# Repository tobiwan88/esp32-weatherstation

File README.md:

# esp32-weatherstation

Solar + USB powered ESP32-S3 air-quality weather station: temperature, humidity, CO2, particulate matter (PM1/2.5/4/10) and a NOx index,
reported over WiFi. Custom 4-layer PCB assembled by JLCPCB. Work in progress: hardware requirements, BOM and checks are in place; layout and firmware come next.

| Part | What |
|---|---|
| MCU | ESP32-S3-WROOM-1-N8, deep-sleep duty cycle (10-15 min) |
| Sensors | Sensirion SEN66 (PM, CO2, T/RH, VOC/NOx index), outdoor SHT45 in a radiation shield, spare Qwiic port |
| Power | one protected 18650, solar MPPT (CN3791) **or** USB-C (TP4056) charging, AP2112K 3.3 V LDO |
| Debug | USB-C native USB-JTAG/serial, UART0 header, test points |
| NO2 | not on v1 (optional external module later) |

Estimated cost: about EUR 240-300 for the first batch (5 boards) plus one complete station, about EUR 133 for each further station
(see `hardware/weatherstation-v1/REQUIREMENTS.md`, section 5a).

## Where to look
- `hardware/weatherstation-v1/`: `REQUIREMENTS.md`, `BOARD.md`, `bom.csv`, `ORDER.md`, `board.yaml`, `parts/`
- `hardware/PLAN.md`: done and next steps. `hardware/README.md`: map of the hardware tree.
- `.claude/skills/`: hardware agent skills (`hw-base`, `kicad-schematic`, `kicad-layout`, `hw-parts`); `CLAUDE.md`: agent notes.
- `scripts/check.sh`: gate (hardware checks, tests, privacy scan).

Base derived from [desk_notifier](https://github.com/tobiwan88/desk_notifier) (hardware skills, calc scripts, tools). MIT license.

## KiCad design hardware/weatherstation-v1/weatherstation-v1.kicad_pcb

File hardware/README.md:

# Hardware: where to look

Board profile: **`weatherstation-v1/`** (requirements, BOM, datasheet cards, order checklist). Pre-layout: no KiCad project yet.

| What | Where |
|---|---|
| Requirements (function, electrical, thermal, EMC, USB, manufacturing, cost) | `weatherstation-v1/REQUIREMENTS.md` |
| BOM with LCSC numbers and verification status | `weatherstation-v1/bom.csv` |
| Board notes, decisions, open items, commands | `weatherstation-v1/BOARD.md` |
| Facts the scripts read | `weatherstation-v1/board.yaml`, `critical.yaml`, `parts/` |
| Order checklist, bring-up | `weatherstation-v1/ORDER.md` |
| Plan and next steps | `PLAN.md` |
| Board-neutral checks | `calc/` (`bom_check.py`, `power_budget.py`, `critical.py`, `buck.py`, `impedance.py`, `pcb.py`) |
| Stock lookup, DRC summary | `tools/` (`jlcparts.py`, `drc_summary.py`) |
| Fab design floors | `rules/` |
| Helper-agent prompts | `agents/` |
| Working KiCad pipeline to copy from (desk_notifier) | `reference/desk_notifier/` |

Agent skills (board-neutral): `hw-base` (read first), `kicad-schematic`, `kicad-layout`, `hw-parts` in `.claude/skills/`.

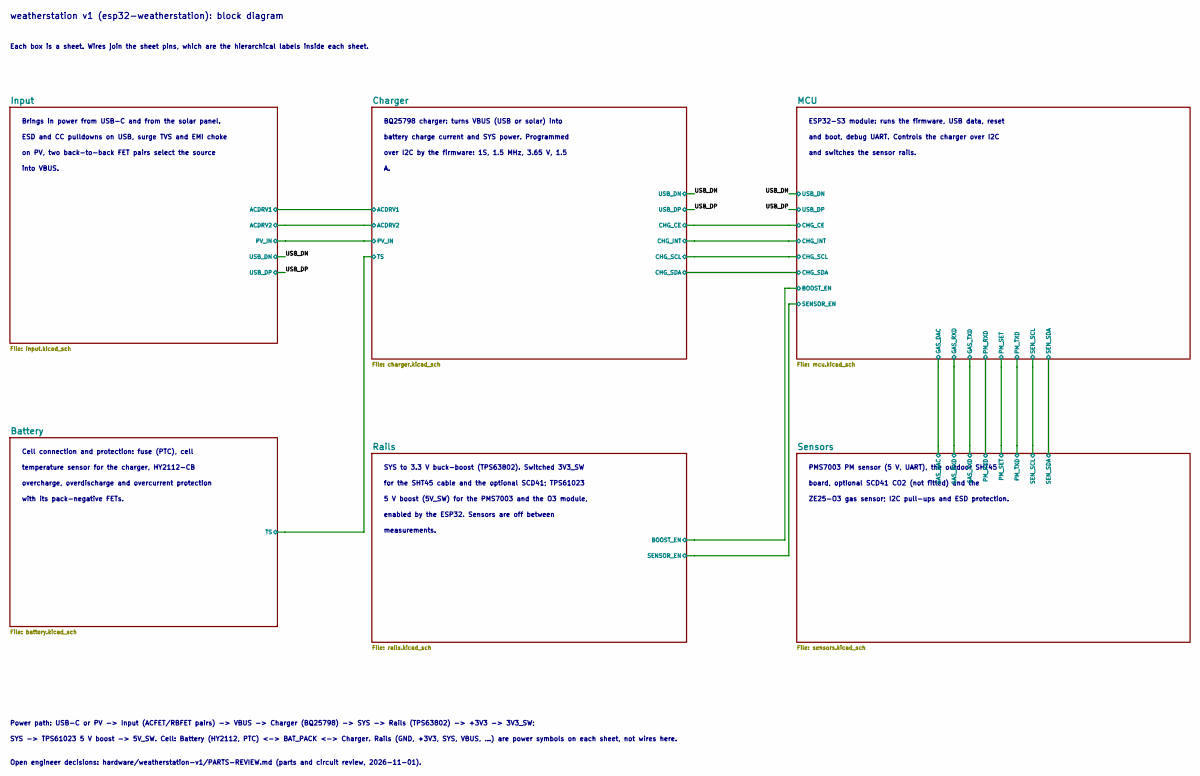
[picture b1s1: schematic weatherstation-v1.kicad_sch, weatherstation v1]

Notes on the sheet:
weatherstation v1 (esp32-weatherstation): block diagram
Each box is a sheet. Wires join the sheet pins, which are the hierarchical labels inside each sheet.
Power path: USB-C or PV -> Input (ACFET/RBFET pairs) -> VBUS -> Charger (BQ25798) -> SYS -> Rails (TPS63802) -> +3V3 -> 3V3_SW;
SYS -> TPS61023 5 V boost -> 5V_SW. Cell: Battery (HY2112, PTC) <-> BAT_PACK <-> Charger. Rails (GND, +3V3, SYS, VBUS, ...) are power symbols on each sheet, not wires here.
Open engineer decisions: hardware/weatherstation-v1/PARTS-REVIEW.md (parts and circuit review, 2026-11-01).
Brings in power from USB-C and from the solar panel.
ESD and CC pulldowns on USB, surge TVS and EMI choke
on PV, two back-to-back FET pairs select the source
into VBUS.
BQ25798 charger: turns VBUS (USB or solar) into
battery charge current and SYS power. Programmed
over I2C by the firmware: 1S, 1.5 MHz, 3.65 V, 1.5
Cell connection and protection: fuse (PTC), cell
temperature sensor for the charger, HY2112-CB
overcharge, overdischarge and overcurrent protection
with its pack-negative FETs.
ESP32-S3 module: runs the firmware, USB data, reset
and boot, debug UART. Controls the charger over I2C
and switches the sensor rails.
SYS to 3.3 V buck-boost (TPS63802). Switched 3V3_SW
for the SHT45 cable and the optional SCD41; TPS61023
5 V boost (5V_SW) for the PMS7003 and the O3 module,
enabled by the ESP32. Sensors are off between
measurements.
PMS7003 PM sensor (5 V, UART), the outdoor SHT45
board, optional SCD41 CO2 (not fitted) and the
ZE25-O3 gas sensor; I2C pull-ups and ESD protection.

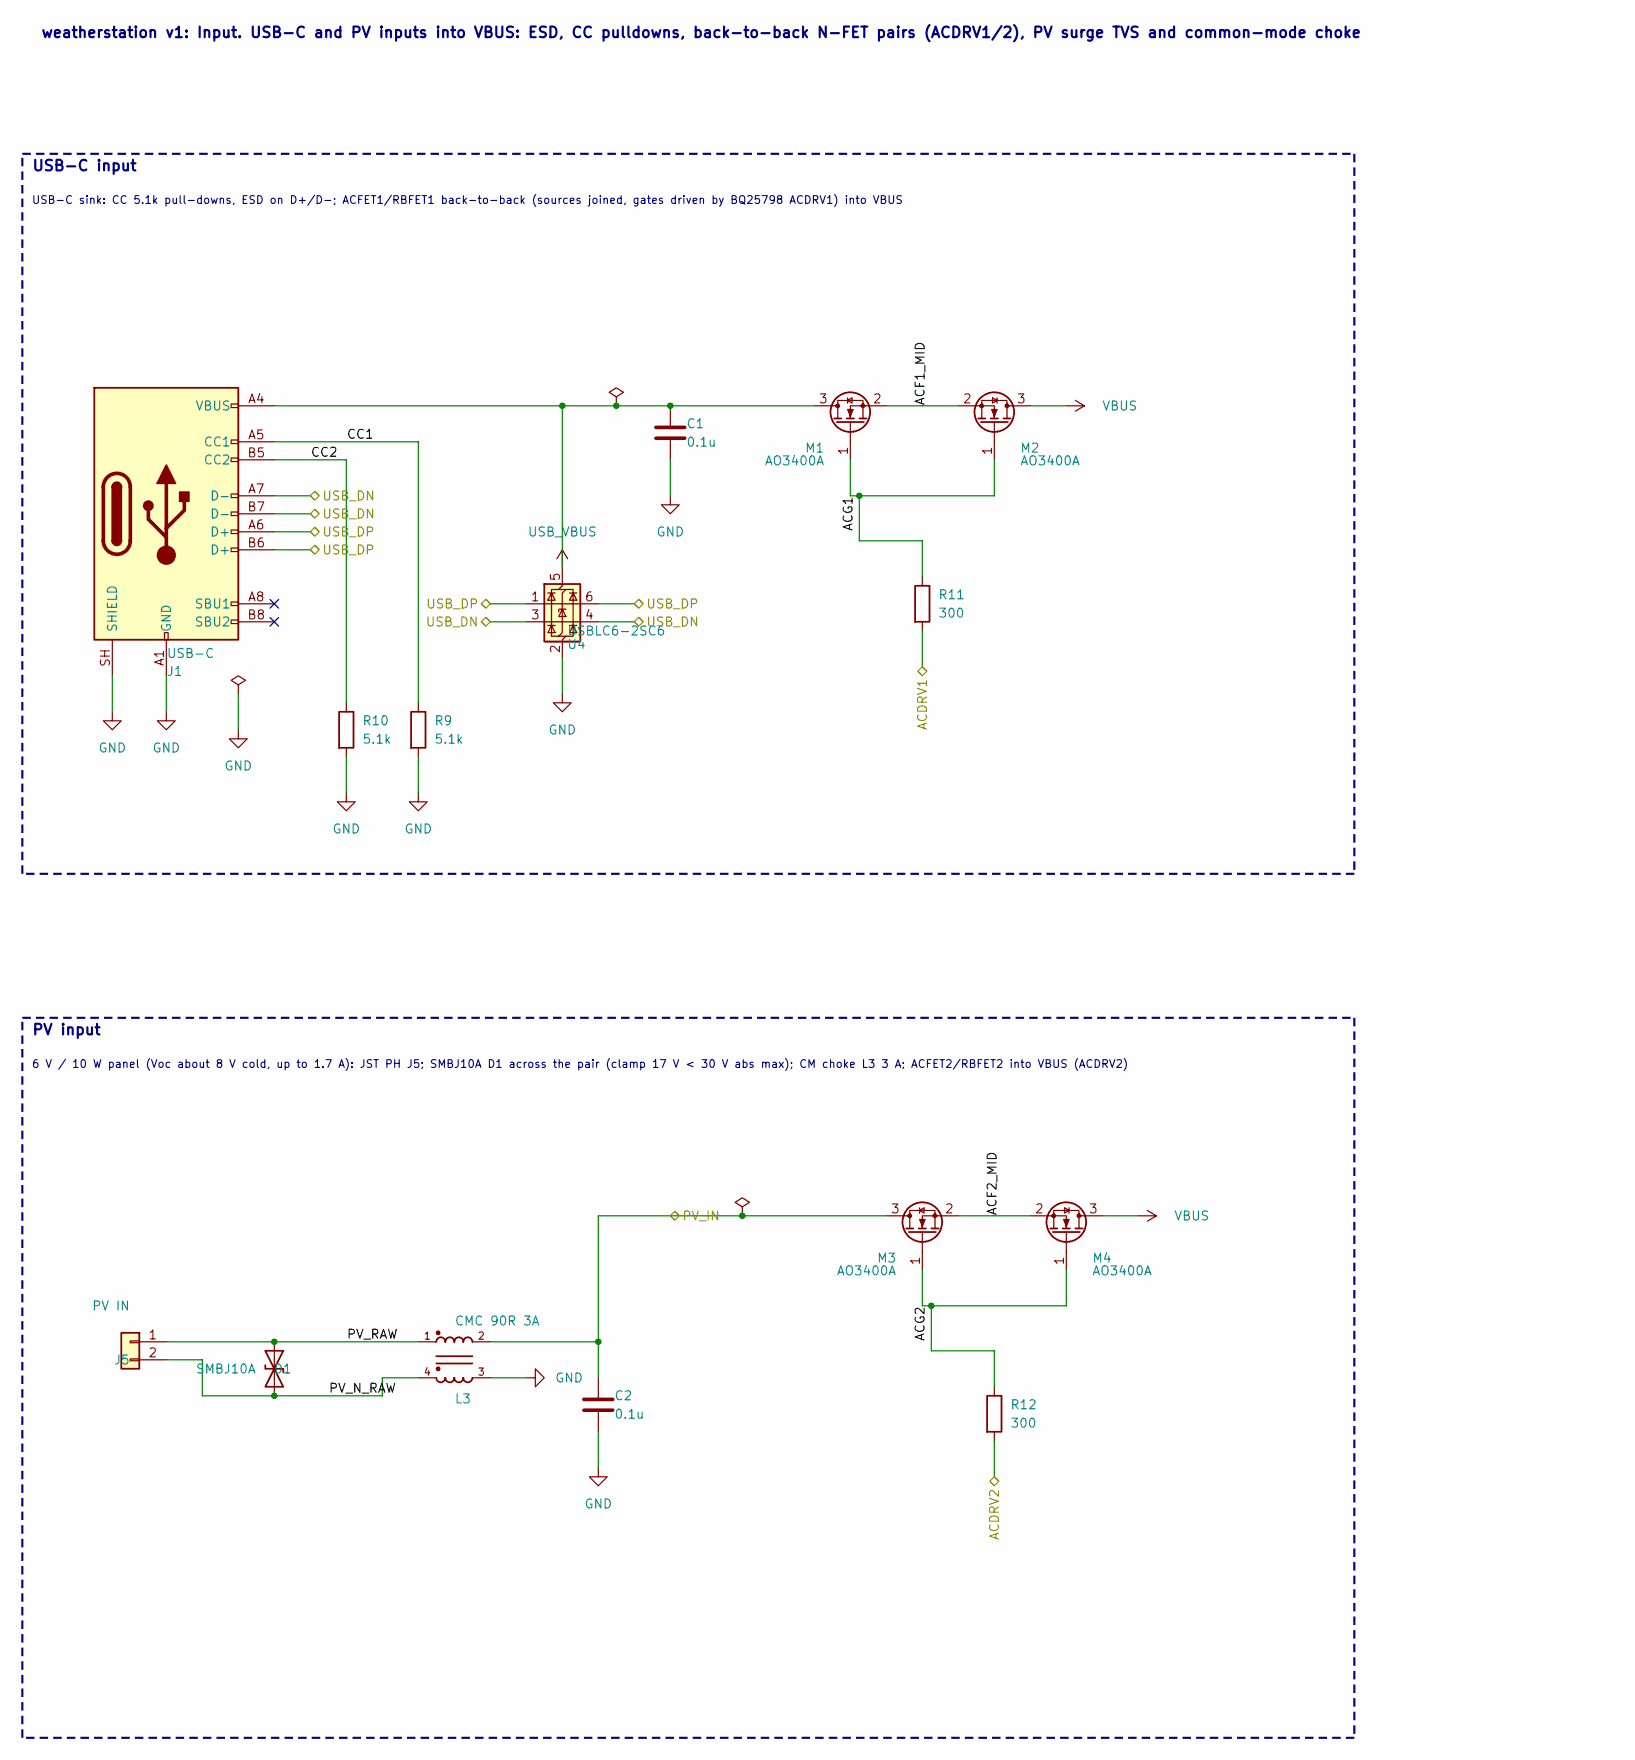
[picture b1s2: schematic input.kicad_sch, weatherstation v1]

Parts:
C1, C2: 0.1u; C_0402_1005Metric; LCSC C307331
D1: SMBJ10A; D_SMB; LCSC C151250
J1: USB-C; USB_C_Receptacle_HRO_TYPE-C-31-M-12; LCSC C165948
J5: PV IN; JST_PH_B2B-PH-K_1x02_P2.00mm_Vertical
L3: CMC 90R 3A; CMF4532F_4P; LCSC C963746
M1, M2, M3, M4: AO3400A; SOT-23; LCSC C20917
R9, R10: 5.1k; R_0402_1005Metric; LCSC C25905
R11, R12: 300; R_0603_1608Metric; LCSC C23025
U4: USBLC6-2SC6; SOT-23-6; LCSC C7519

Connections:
/Charger/ACDRV1: R11.2; also elsewhere on the board
/Charger/ACDRV2: R12.2; also elsewhere on the board
/Charger/PV_IN: C2.1, L3.2, M3.3 (D); also elsewhere on the board
/Input/ACF1_MID: M1.2 (S), M2.2 (S)
/Input/ACF2_MID: M3.2 (S), M4.2 (S)
/Input/ACG1: M1.1 (G), M2.1 (G), R11.1
/Input/ACG2: M3.1 (G), M4.1 (G), R12.1
/Input/CC1: J1.A5 (CC1), R9.1
/Input/CC2: J1.B5 (CC2), R10.1
/Input/PV_N_RAW: D1.2 (A2), J5.2, L3.4
/Input/PV_RAW: D1.1 (A1), J5.1, L3.1
/USB_DN: J1.A7 (D-), J1.B7 (D-), U4.3 (I/O2), U4.4 (I/O2); also elsewhere on the board
/USB_DP: J1.A6 (D+), J1.B6 (D+), U4.1 (I/O1), U4.6 (I/O1); also elsewhere on the board
GND: C1.2, C2.2, J1.A1 (GND), J1.A12 (GND), J1.B1 (GND), J1.B12 (GND), J1.SH (SHIELD), L3.3, R9.2, R10.2, U4.2 (GND); also elsewhere on the board
USB_VBUS: C1.1, J1.A4 (VBUS), J1.A9 (VBUS), J1.B4 (VBUS), J1.B9 (VBUS), M1.3 (D), U4.5 (VBUS); also elsewhere on the board
VBUS: M2.3 (D), M4.3 (D); also elsewhere on the board

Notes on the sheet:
USB-C input
USB-C sink: CC 5.1k pull-downs, ESD on D+/D-; ACFET1/RBFET1 back-to-back (sources joined, gates driven by BQ25798 ACDRV1) into VBUS
PV input
6 V / 10 W panel (Voc about 8 V cold, up to 1.7 A): JST PH J5; SMBJ10A D1 across the pair (clamp 17 V < 30 V abs max); CM choke L3 3 A; ACFET2/RBFET2 into VBUS (ACDRV2)
weatherstation v1: Input. USB-C and PV inputs into VBUS: ESD, CC pulldowns, back-to-back N-FET pairs (ACDRV1/2), PV surge TVS and common-mode choke

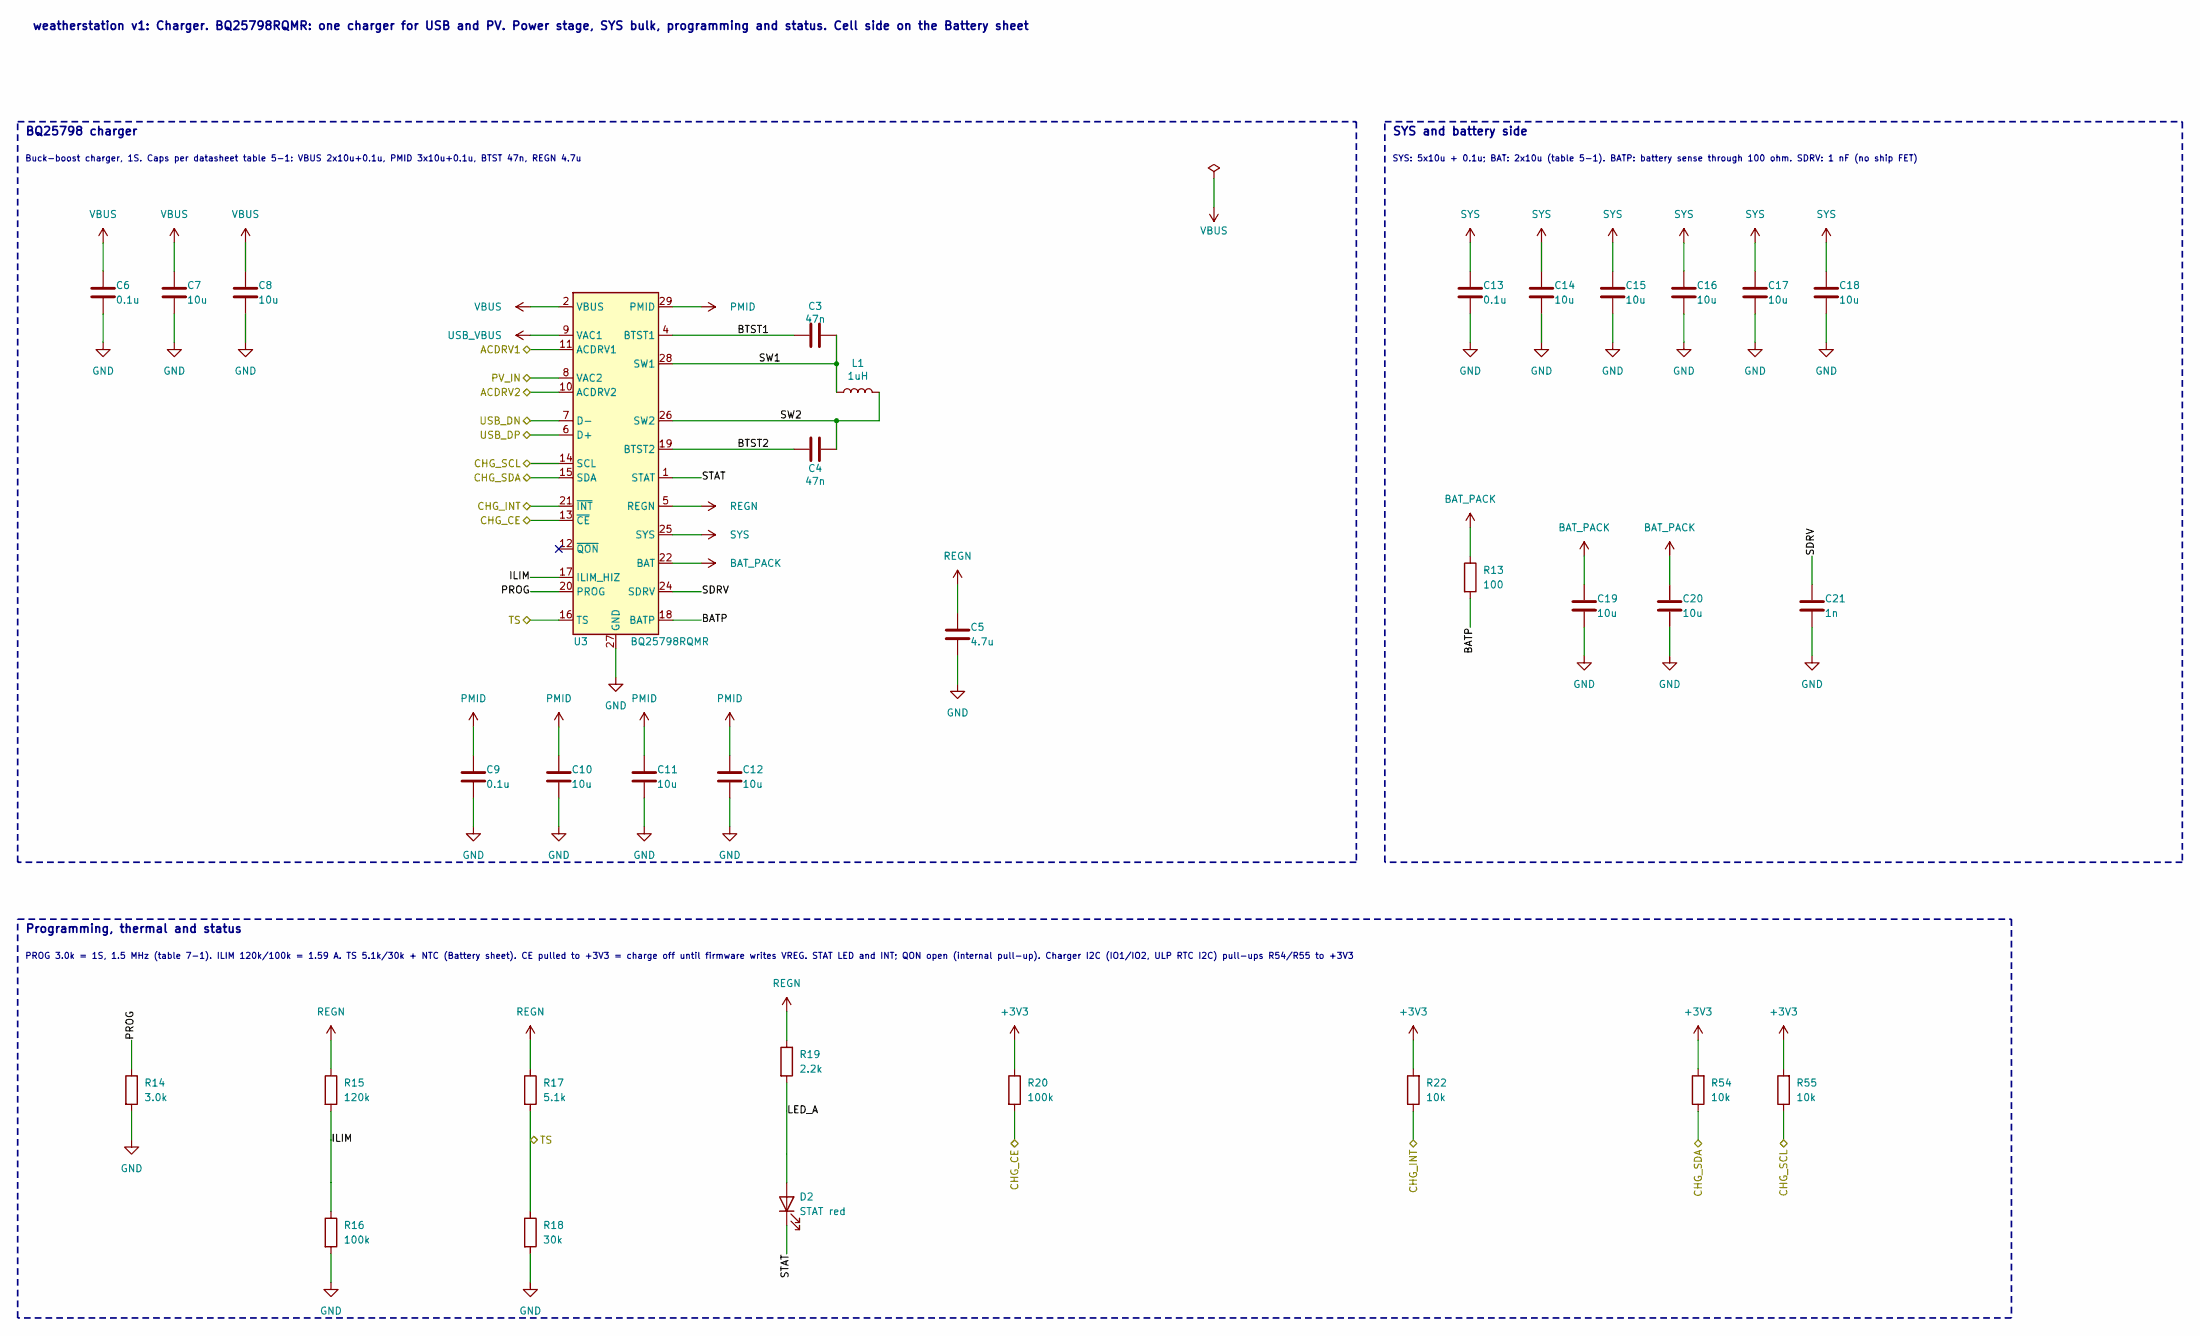
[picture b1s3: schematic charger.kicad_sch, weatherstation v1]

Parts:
C3, C4: 47n; C_0603_1608Metric; LCSC C1622
C5: 4.7u; C_0603_1608Metric; LCSC C19666
C6, C9, C13: 0.1u; C_0402_1005Metric; LCSC C307331
C7, C8, C10, C11, C12, C14, C15, C16, C17, C18, C19, C20: 10u; C_0805_2012Metric; LCSC C15850
C21: 1n; C_0402_1005Metric; LCSC C1523
D2: STAT red; LED_0603_1608Metric; LCSC C2286
L1: 1uH; L_TDK_VLS252010; LCSC C88211
R13: 100; R_0402_1005Metric; LCSC C25076
R14: 3.0k; R_0603_1608Metric; LCSC C4211
R15: 120k; R_0603_1608Metric; LCSC C25808
R16, R20: 100k; R_0402_1005Metric; LCSC C25741
R17: 5.1k; R_0402_1005Metric; LCSC C25905
R18: 30k; R_0603_1608Metric; LCSC C22984
R19: 2.2k; R_0402_1005Metric; LCSC C25879
R22, R54, R55: 10k; R_0402_1005Metric; LCSC C25744
U3: BQ25798RQMR; Texas_RQM0029A_VQFN-29_4x4mm_P0.4mm; LCSC C2876593

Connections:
+3V3: R20.1, R22.2, R54.2, R55.2; also elsewhere on the board
/Battery/TS: R17.2, R18.1, U3.16 (TS); also elsewhere on the board
/Charger/ACDRV1: U3.11 (ACDRV1); also elsewhere on the board
/Charger/ACDRV2: U3.10 (ACDRV2); also elsewhere on the board
/Charger/BATP: R13.2, U3.18 (BATP)
/Charger/BTST1: C3.1, U3.4 (BTST1)
/Charger/BTST2: C4.1, U3.19 (BTST2)
/Charger/CHG_CE: R20.2, U3.13 (~CE); also elsewhere on the board
/Charger/CHG_INT: R22.1, U3.21 (~INT); also elsewhere on the board
/Charger/CHG_SCL: R55.1, U3.14 (SCL); also elsewhere on the board
/Charger/CHG_SDA: R54.1, U3.15 (SDA); also elsewhere on the board
/Charger/ILIM: R15.2, R16.1, U3.17 (ILIM_HIZ)
/Charger/LED_A: D2.2 (A), R19.2
/Charger/PROG: R14.1, U3.20 (PROG)
/Charger/PV_IN: U3.8 (VAC2); also elsewhere on the board
/Charger/SDRV: C21.1, U3.24 (SDRV)
/Charger/STAT: D2.1 (K), U3.1 (STAT)
/Charger/SW1: C3.2, L1.1, U3.28 (SW1)
/Charger/SW2: C4.2, L1.2, U3.26 (SW2)
/USB_DN: U3.7 (D-); also elsewhere on the board
/USB_DP: U3.6 (D+); also elsewhere on the board
BAT_PACK: C19.1, C20.1, R13.1, U3.22 (BAT), U3.23 (BAT); also elsewhere on the board
GND: C5.2, C6.2, C7.2, C8.2, C9.2, C10.2, C11.2, C12.2, C13.2, C14.2, C15.2, C16.2, C17.2, C18.2, C19.2, C20.2, C21.2, R14.2, R16.2, R18.2, U3.27 (GND); also elsewhere on the board
PMID: C9.1, C10.1, C11.1, C12.1, U3.29 (PMID)
REGN: C5.1, R15.1, R17.1, R19.1, U3.5 (REGN)
SYS: C13.1, C14.1, C15.1, C16.1, C17.1, C18.1, U3.25 (SYS); also elsewhere on the board
USB_VBUS: U3.9 (VAC1); also elsewhere on the board
VBUS: C6.1, C7.1, C8.1, U3.2 (VBUS), U3.3 (VBUS); also elsewhere on the board

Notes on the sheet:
BQ25798 charger
Buck-boost charger, 1S. Caps per datasheet table 5-1: VBUS 2x10u+0.1u, PMID 3x10u+0.1u, BTST 47n, REGN 4.7u
SYS and battery side
SYS: 5x10u + 0.1u; BAT: 2x10u (table 5-1). BATP: battery sense through 100 ohm. SDRV: 1 nF (no ship FET)
Programming, thermal and status
PROG 3.0k = 1S, 1.5 MHz (table 7-1). ILIM 120k/100k = 1.59 A. TS 5.1k/30k + NTC (Battery sheet). CE pulled to +3V3 = charge off until firmware writes VREG. STAT LED and INT; QON open (internal pull-up). Charger I2C (IO1/IO2, ULP RTC I2C) pull-ups R54/R55 to +3V3
weatherstation v1: Charger. BQ25798RQMR: one charger for USB and PV. Power stage, SYS bulk, programming and status. Cell side on the Battery sheet

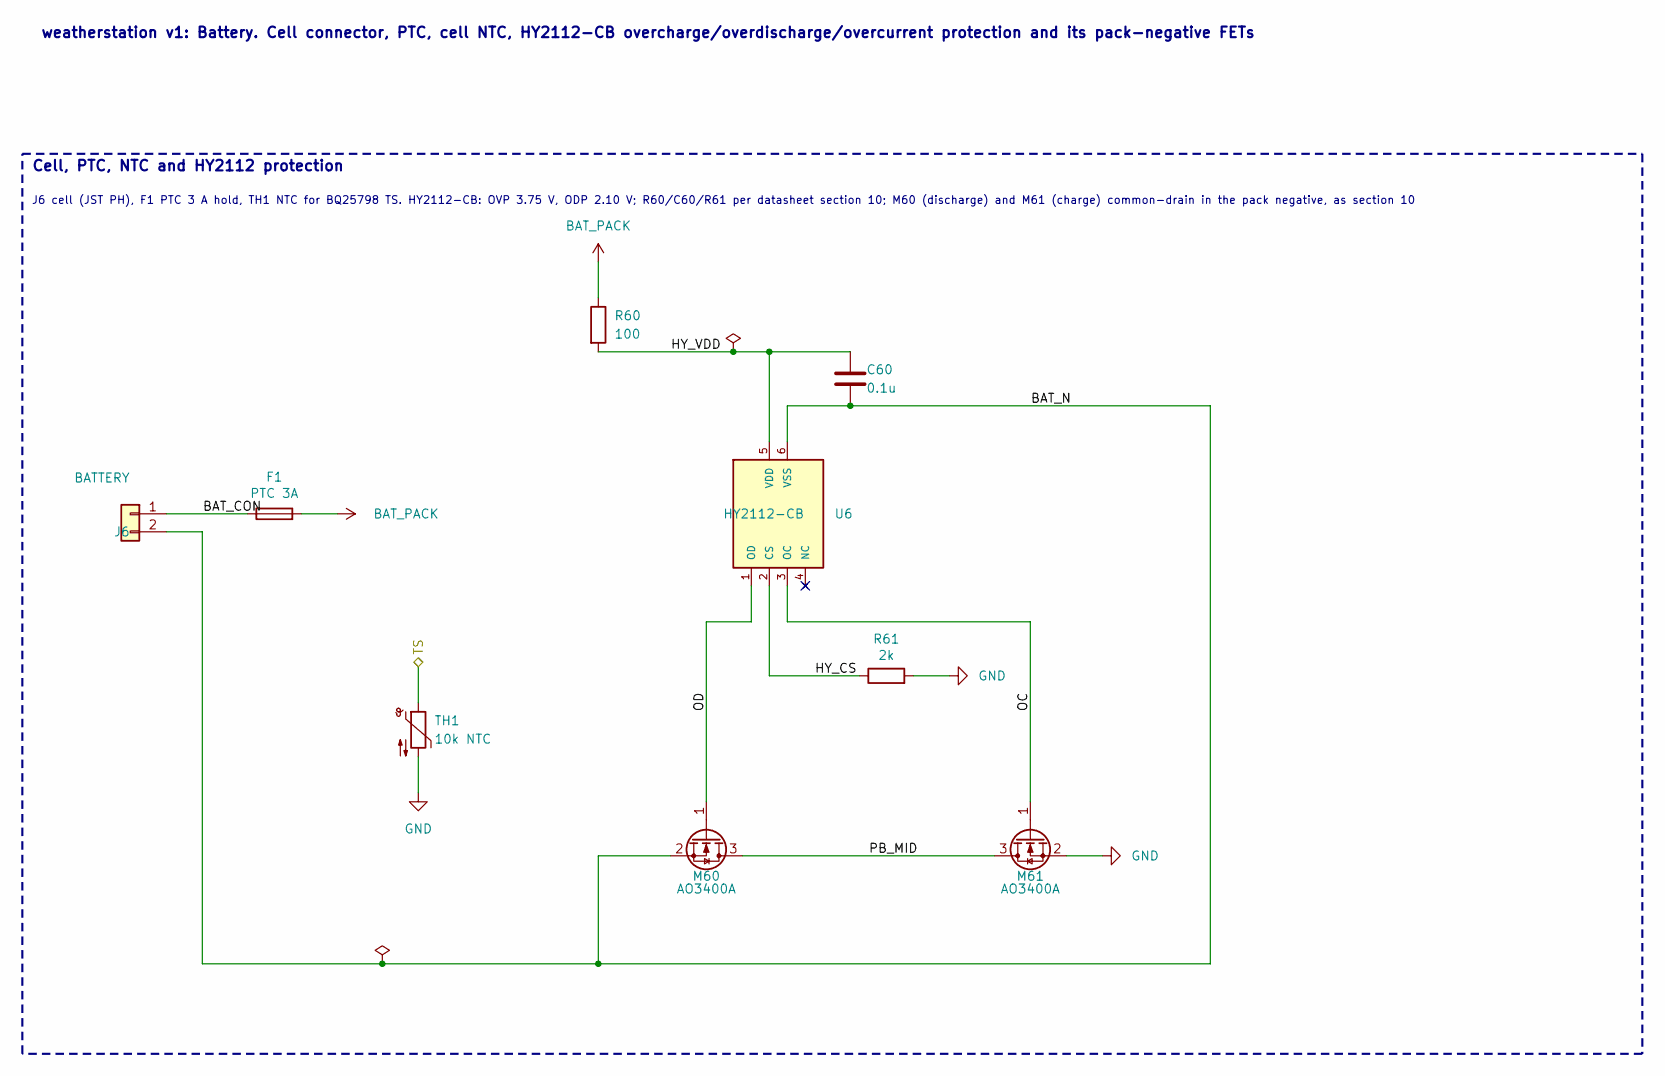
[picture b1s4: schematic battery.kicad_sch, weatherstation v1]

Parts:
C60: 0.1u; C_0402_1005Metric; LCSC C307331
F1: PTC 3A; Fuse_1812_4532Metric; LCSC C21004
J6: BATTERY; JST_PH_B2B-PH-K_1x02_P2.00mm_Vertical
M60, M61: AO3400A; SOT-23; LCSC C20917
R60: 100; R_0402_1005Metric; LCSC C25076
R61: 2k; R_0402_1005Metric; LCSC C4109
TH1: 10k NTC; R_0603_1608Metric; LCSC C13564
U6: HY2112-CB; SOT-23-6; LCSC C168764

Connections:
/Battery/BAT_CON: F1.1, J6.1
/Battery/BAT_N: C60.2, J6.2, M60.2 (S), U6.6 (VSS)
/Battery/HY_CS: R61.1, U6.2 (CS)
/Battery/HY_VDD: C60.1, R60.2, U6.5 (VDD)
/Battery/OC: M61.1 (G), U6.3 (OC)
/Battery/OD: M60.1 (G), U6.1 (OD)
/Battery/PB_MID: M60.3 (D), M61.3 (D)
/Battery/TS: TH1.1; also elsewhere on the board
BAT_PACK: F1.2, R60.1; also elsewhere on the board
GND: M61.2 (S), R61.2, TH1.2; also elsewhere on the board

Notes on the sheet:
Cell, PTC, NTC and HY2112 protection
J6 cell (JST PH), F1 PTC 3 A hold, TH1 NTC for BQ25798 TS. HY2112-CB: OVP 3.75 V, ODP 2.10 V; R60/C60/R61 per datasheet section 10; M60 (discharge) and M61 (charge) common-drain in the pack negative, as section 10
weatherstation v1: Battery. Cell connector, PTC, cell NTC, HY2112-CB overcharge/overdischarge/overcurrent protection and its pack-negative FETs

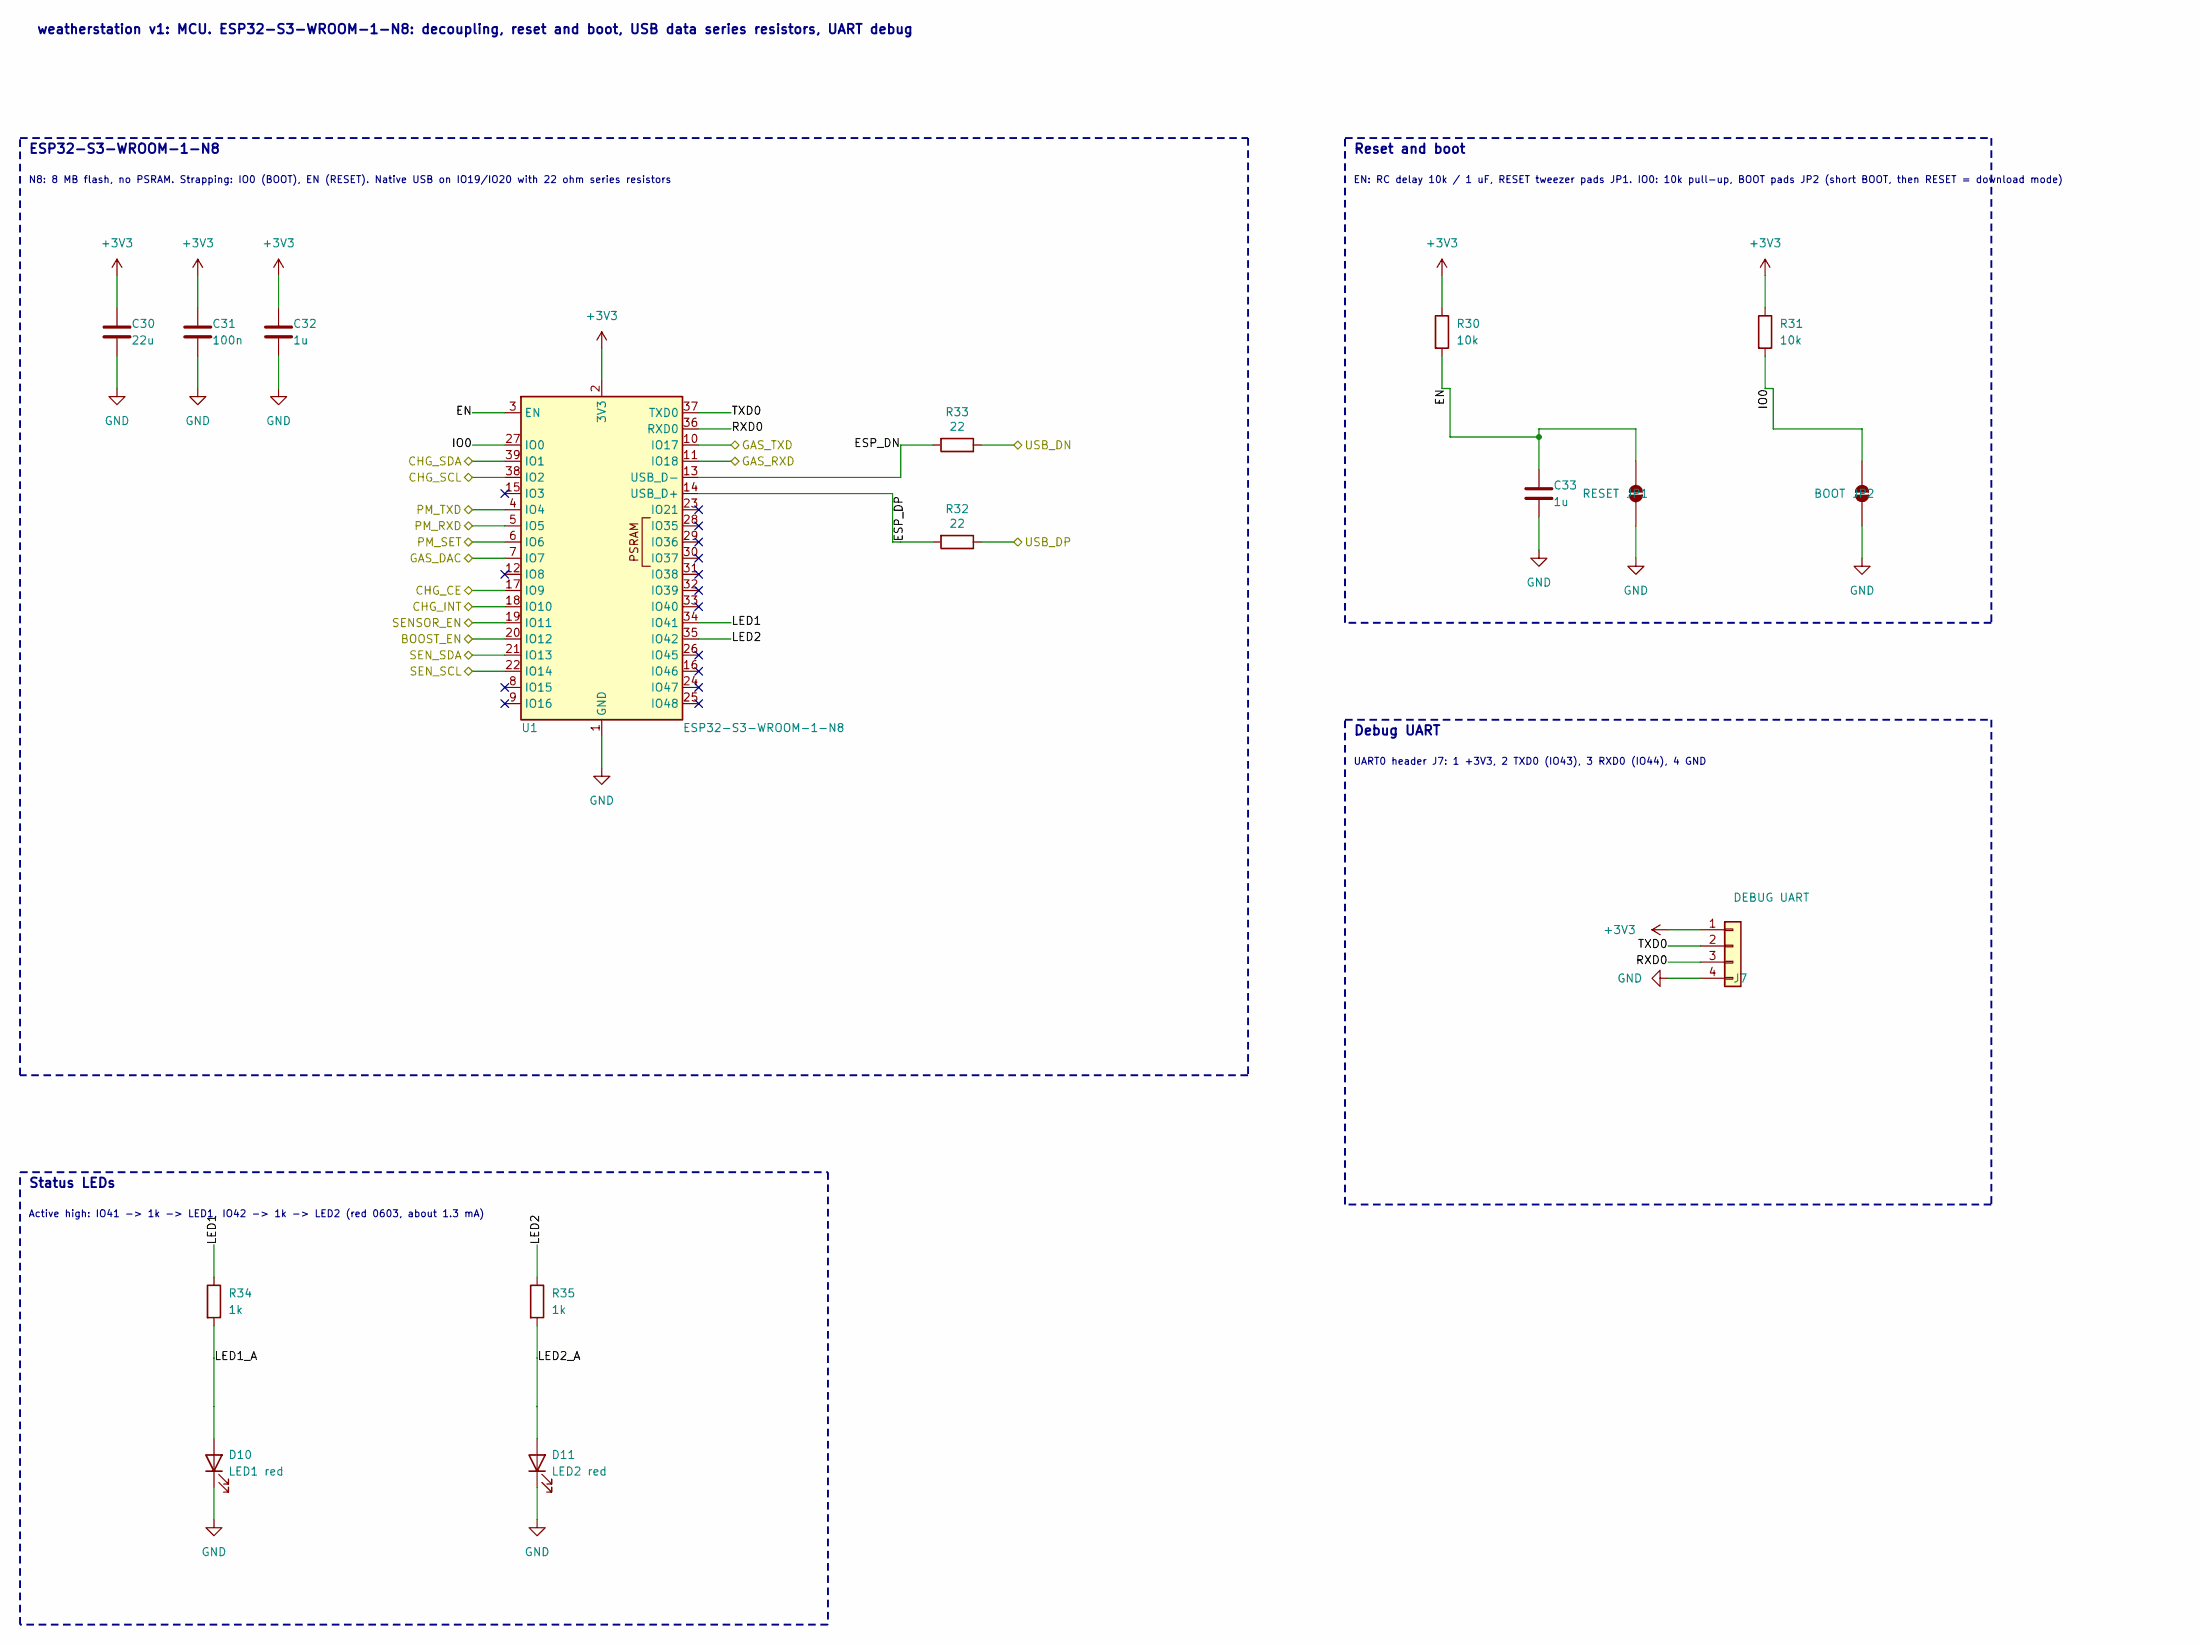
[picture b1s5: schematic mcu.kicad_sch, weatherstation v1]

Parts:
C30: 22u; C_0805_2012Metric; LCSC C45783
C31: 100n; C_0402_1005Metric; LCSC C307331
C32, C33: 1u; C_0402_1005Metric; LCSC C52923
D10: LED1 red; LED_0603_1608Metric; LCSC C2286
D11: LED2 red; LED_0603_1608Metric; LCSC C2286
J7: DEBUG UART; PinHeader_1x04_P2.54mm_Vertical
JP1: RESET; SolderJumper-2_P1.3mm_Open_RoundedPad1.0x1.5mm
JP2: BOOT; SolderJumper-2_P1.3mm_Open_RoundedPad1.0x1.5mm
R30, R31: 10k; R_0402_1005Metric; LCSC C25744
R32, R33: 22; R_0402_1005Metric; LCSC C25092
R34, R35: 1k; R_0402_1005Metric; LCSC C11702
U1: ESP32-S3-WROOM-1-N8; ESP32-S3-WROOM-1; LCSC C2913198

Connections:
+3V3: C30.1, C31.1, C32.1, J7.1, R30.1, R31.1, U1.2 (3V3); also elsewhere on the board
/Charger/CHG_CE: U1.17 (IO9); also elsewhere on the board
/Charger/CHG_INT: U1.18 (IO10); also elsewhere on the board
/Charger/CHG_SCL: U1.38 (IO2); also elsewhere on the board
/Charger/CHG_SDA: U1.39 (IO1); also elsewhere on the board
/MCU/BOOST_EN: U1.20 (IO12); also elsewhere on the board
/MCU/EN: C33.1, JP1.1 (A), R30.2, U1.3 (EN)
/MCU/ESP_DN: R33.2, U1.13 (USB_D-)
/MCU/ESP_DP: R32.2, U1.14 (USB_D+)
/MCU/GAS_DAC: U1.7 (IO7); also elsewhere on the board
/MCU/GAS_RXD: U1.11 (IO18); also elsewhere on the board
/MCU/GAS_TXD: U1.10 (IO17); also elsewhere on the board
/MCU/IO0: JP2.1 (A), R31.2, U1.27 (IO0)
/MCU/LED1: R34.1, U1.34 (IO41)
/MCU/LED1_A: D10.2 (A), R34.2
/MCU/LED2: R35.1, U1.35 (IO42)
/MCU/LED2_A: D11.2 (A), R35.2
/MCU/PM_RXD: U1.5 (IO5); also elsewhere on the board
/MCU/PM_SET: U1.6 (IO6); also elsewhere on the board
/MCU/PM_TXD: U1.4 (IO4); also elsewhere on the board
/MCU/RXD0: J7.3, U1.36 (RXD0)
/MCU/SENSOR_EN: U1.19 (IO11); also elsewhere on the board
/MCU/SEN_SCL: U1.22 (IO14); also elsewhere on the board
/MCU/SEN_SDA: U1.21 (IO13); also elsewhere on the board
/MCU/TXD0: J7.2, U1.37 (TXD0)
/USB_DN: R33.1; also elsewhere on the board
/USB_DP: R32.1; also elsewhere on the board
GND: C30.2, C31.2, C32.2, C33.2, D10.1 (K), D11.1 (K), J7.4, JP1.2 (B), JP2.2 (B), U1.1 (GND), U1.40 (GND), U1.41 (GND); also elsewhere on the board

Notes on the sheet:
ESP32-S3-WROOM-1-N8
N8: 8 MB flash, no PSRAM. Strapping: IO0 (BOOT), EN (RESET). Native USB on IO19/IO20 with 22 ohm series resistors
Reset and boot
EN: RC delay 10k / 1 uF, RESET tweezer pads JP1. IO0: 10k pull-up, BOOT pads JP2 (short BOOT, then RESET = download mode)
Debug UART
UART0 header J7: 1 +3V3, 2 TXD0 (IO43), 3 RXD0 (IO44), 4 GND
Status LEDs
Active high: IO41 -> 1k -> LED1, IO42 -> 1k -> LED2 (red 0603, about 1.3 mA)
weatherstation v1: MCU. ESP32-S3-WROOM-1-N8: decoupling, reset and boot, USB data series resistors, UART debug

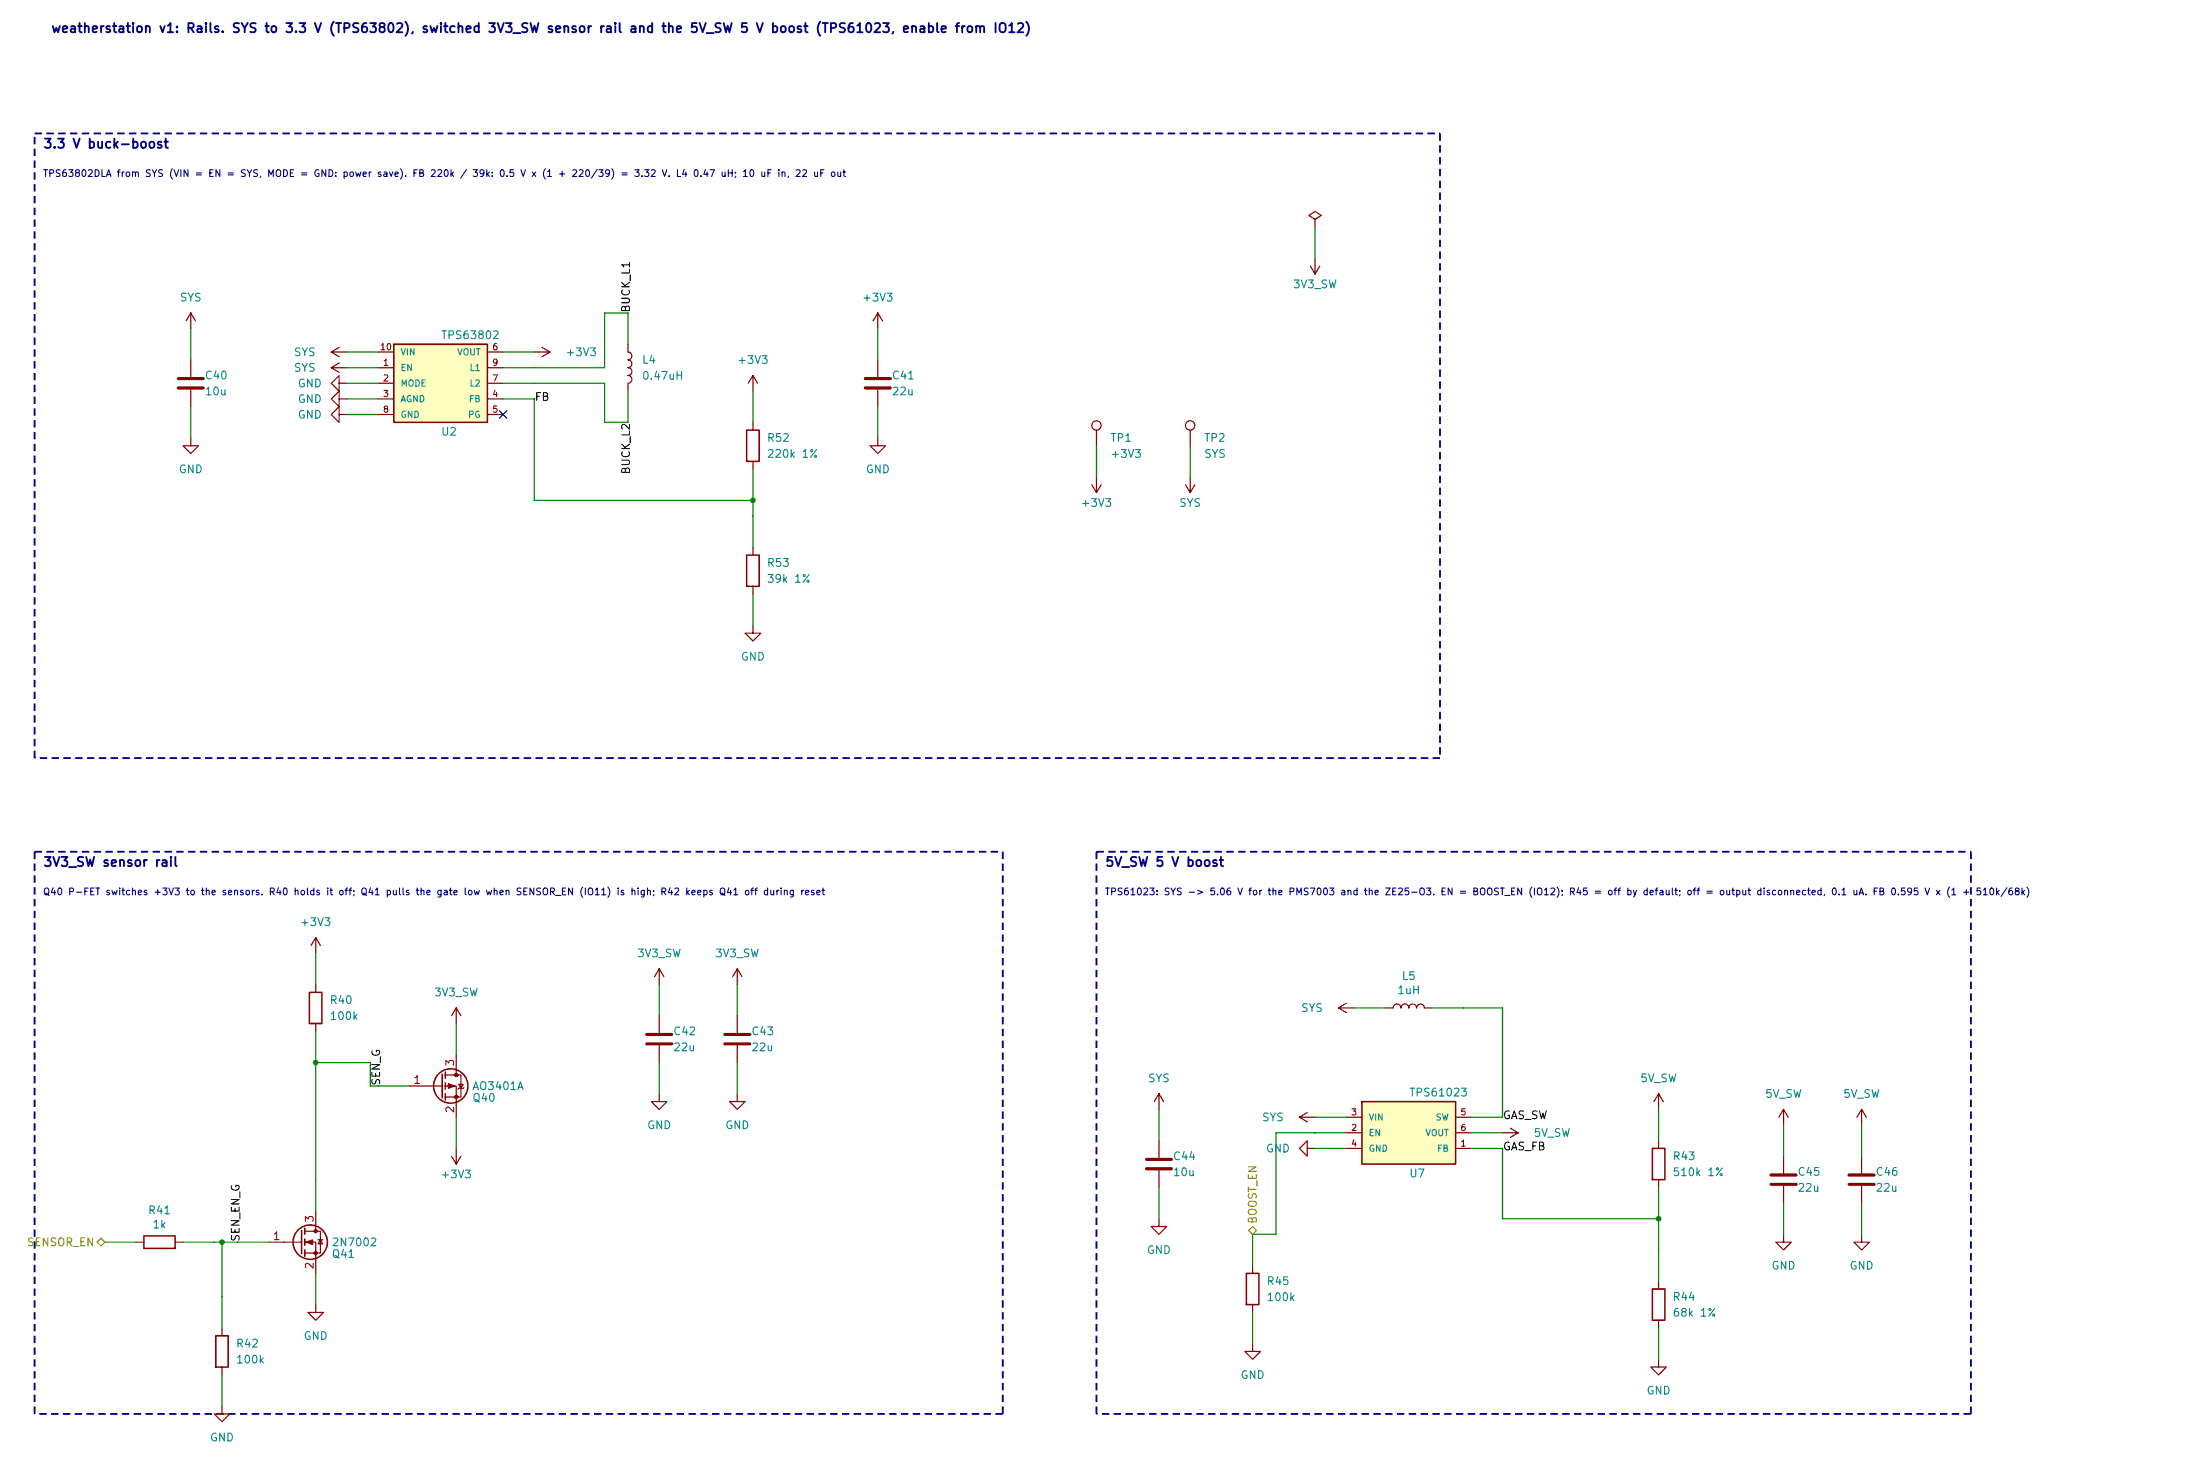
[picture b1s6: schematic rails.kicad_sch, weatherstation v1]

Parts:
C40, C44: 10u; C_0603_1608Metric; LCSC C19702
C41, C42, C43, C45, C46: 22u; C_0805_2012Metric; LCSC C45783
L4: 0.47uH; L_Sunlord_WPN201610H; LCSC C97009
L5: 1uH; L_TDK_VLS252010; LCSC C88211
Q40: AO3401A; SOT-23; LCSC C15127
Q41: 2N7002; SOT-23; LCSC C8545
R40, R42, R45: 100k; R_0402_1005Metric; LCSC C25741
R41: 1k; R_0402_1005Metric; LCSC C11702
R43: 510k 1%; R_0603_1608Metric; LCSC C23192
R44: 68k 1%; R_0603_1608Metric; LCSC C23231
R52: 220k 1%; R_0603_1608Metric; LCSC C22961
R53: 39k 1%; R_0603_1608Metric; LCSC C23153
TP1: +3V3; TestPoint_Pad_D1.5mm
TP2: SYS; TestPoint_Pad_D1.5mm
U2: TPS63802; TPS63802_DLA_VSON-HR-10_2x3mm; LCSC C2845237
U7: TPS61023; SOT-563; LCSC C919459

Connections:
3V3_SW: C42.1, C43.1, Q40.3 (D); also elsewhere on the board
5V_SW: C45.1, C46.1, R43.1, U7.6 (VOUT); also elsewhere on the board
+3V3: C41.1, Q40.2 (S), R40.1, R52.1, TP1.1, U2.6 (VOUT); also elsewhere on the board
/MCU/BOOST_EN: R45.1, U7.2 (EN); also elsewhere on the board
/MCU/SENSOR_EN: R41.1; also elsewhere on the board
/Rails/BUCK_L1: L4.1, U2.9 (L1)
/Rails/BUCK_L2: L4.2, U2.7 (L2)
/Rails/FB: R52.2, R53.1, U2.4 (FB)
/Rails/GAS_FB: R43.2, R44.1, U7.1 (FB)
/Rails/GAS_SW: L5.2, U7.5 (SW)
/Rails/SEN_EN_G: Q41.1 (G), R41.2, R42.1
/Rails/SEN_G: Q40.1 (G), Q41.3 (D), R40.2
GND: C40.2, C41.2, C42.2, C43.2, C44.2, C45.2, C46.2, Q41.2 (S), R42.2, R44.2, R45.2, R53.2, U2.2 (MODE), U2.3 (AGND), U2.8 (GND), U7.4 (GND); also elsewhere on the board
SYS: C40.1, C44.1, L5.1, TP2.1, U2.1 (EN), U2.10 (VIN), U7.3 (VIN); also elsewhere on the board

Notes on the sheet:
3.3 V buck-boost
TPS63802DLA from SYS (VIN = EN = SYS, MODE = GND: power save). FB 220k / 39k: 0.5 V x (1 + 220/39) = 3.32 V. L4 0.47 uH; 10 uF in, 22 uF out
3V3_SW sensor rail
Q40 P-FET switches +3V3 to the sensors. R40 holds it off; Q41 pulls the gate low when SENSOR_EN (IO11) is high; R42 keeps Q41 off during reset
5V_SW 5 V boost
TPS61023: SYS -> 5.06 V for the PMS7003 and the ZE25-O3. EN = BOOST_EN (IO12); R45 = off by default; off = output disconnected, 0.1 uA. FB 0.595 V x (1 + 510k/68k)
weatherstation v1: Rails. SYS to 3.3 V (TPS63802), switched 3V3_SW sensor rail and the 5V_SW 5 V boost (TPS61023, enable from IO12)
